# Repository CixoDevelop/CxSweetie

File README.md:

# CxSweetie
This is so sweet tamagotchi based on 7-segment screen!

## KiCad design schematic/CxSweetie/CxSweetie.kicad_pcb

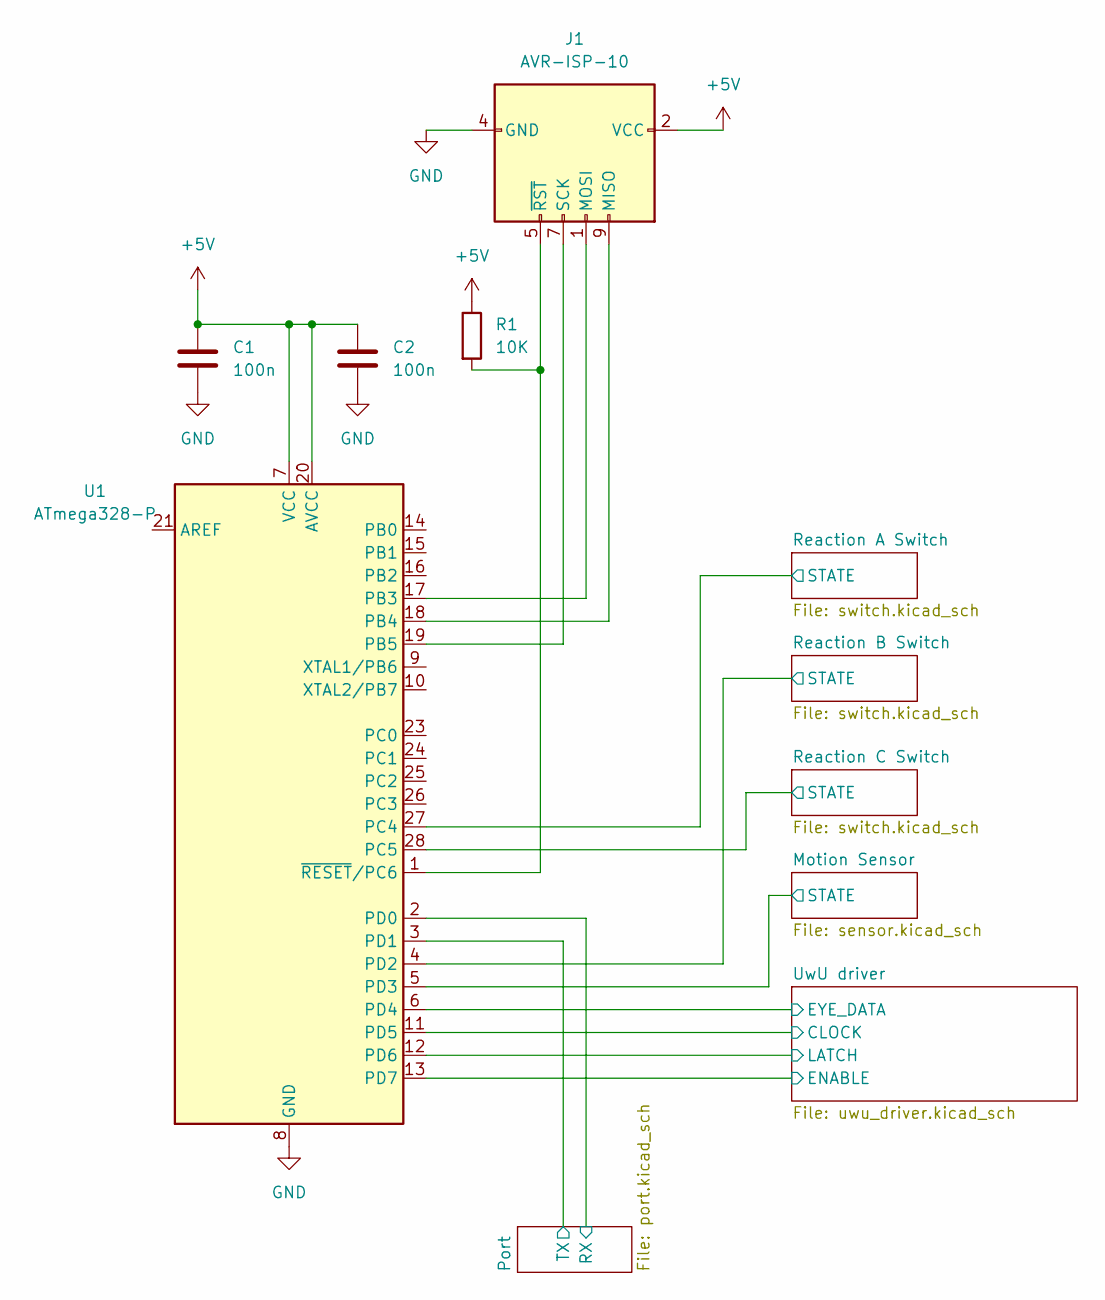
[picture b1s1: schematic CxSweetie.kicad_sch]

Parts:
C1, C2: 100n; CP_Radial_D6.3mm_P2.50mm
J1: AVR-ISP-10; PinHeader_2x05_P2.54mm_Vertical
R1: 10K; R_Axial_DIN0207_L6.3mm_D2.5mm_P7.62mm_Horizontal
U1: ATmega328-P; DIP-28_W7.62mm

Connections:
+5V: C1.1, C2.1, J1.2 (VCC), R1.1, U1.7 (VCC), U1.20 (AVCC); also elsewhere on the board
/Motion Sensor/STATE: U1.5 (PD3); also elsewhere on the board
/Port/RX: U1.2 (PD0); also elsewhere on the board
/Port/TX: U1.3 (PD1); also elsewhere on the board
/Reaction A Switch/STATE: U1.27 (PC4); also elsewhere on the board
/Reaction B Switch/STATE: U1.4 (PD2); also elsewhere on the board
/Reaction C Switch/STATE: U1.28 (PC5); also elsewhere on the board
/UwU driver/CLOCK: U1.11 (PD5); also elsewhere on the board
/UwU driver/ENABLE: U1.13 (PD7); also elsewhere on the board
/UwU driver/EYE_DATA: U1.6 (PD4); also elsewhere on the board
/UwU driver/LATCH: U1.12 (PD6); also elsewhere on the board
GND: C1.2, C2.2, J1.4 (GND), J1.6 (GND), J1.8 (GND), J1.10 (GND), U1.8 (GND), U1.22 (GND); also elsewhere on the board
unnamed: J1.1 (MOSI), U1.17 (PB3)
unnamed: J1.5 (~RST), R1.2, U1.1 (~RESET/PC6)
unnamed: J1.7 (SCK), U1.19 (PB5)
unnamed: J1.9 (MISO), U1.18 (PB4)

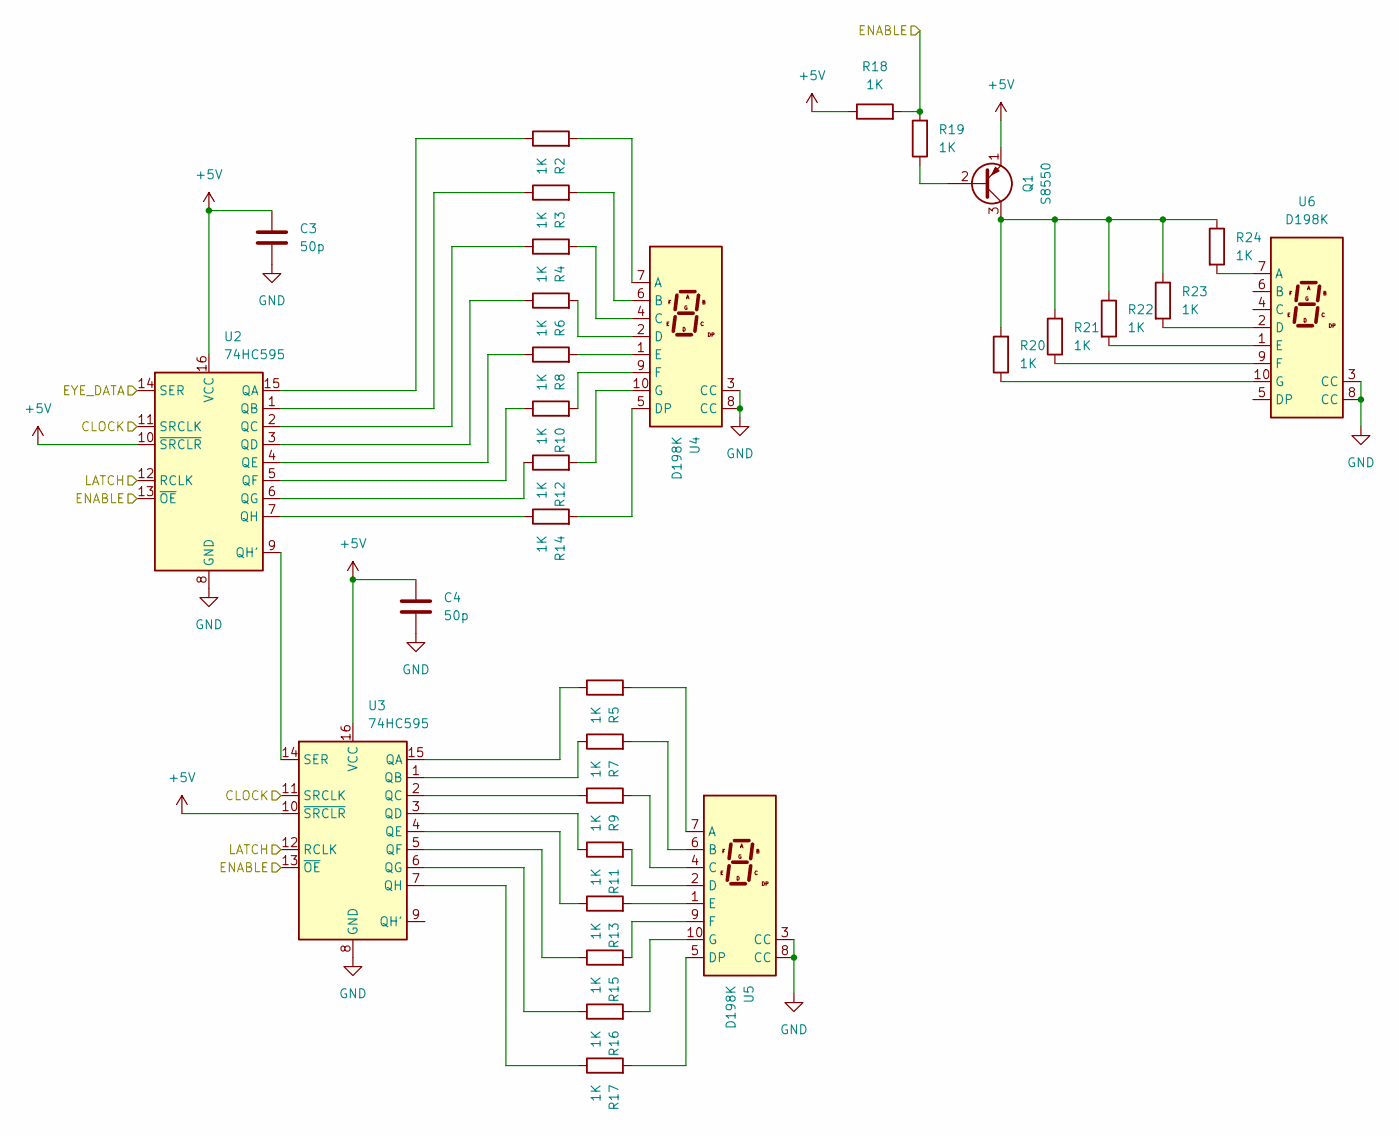
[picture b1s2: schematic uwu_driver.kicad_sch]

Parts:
C3, C4: 50p; CP_Radial_D6.3mm_P2.50mm
Q1: S8550; TO-92_Inline
R2, R3, R4, R5, R6, R7, R8, R9, R10, R11, R12, R13, R14, R15, R16, R17, R18, R19, R20, R21, R22, R23, R24: 1K; R_Axial_DIN0207_L6.3mm_D2.5mm_P7.62mm_Horizontal
U2, U3: 74HC595; DIP-16_W7.62mm
U4, U5, U6: D198K; 7SegmentLED_LTS6760_LTS6780

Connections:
+5V: C3.1, C4.1, Q1.1 (E), R18.1, U2.10 (~SRCLR), U2.16 (VCC), U3.10 (~SRCLR), U3.16 (VCC); also elsewhere on the board
/UwU driver/CLOCK: U2.11 (SRCLK), U3.11 (SRCLK); also elsewhere on the board
/UwU driver/ENABLE: R18.2, R19.2, U2.13 (~OE), U3.13 (~OE); also elsewhere on the board
/UwU driver/EYE_DATA: U2.14 (SER); also elsewhere on the board
/UwU driver/LATCH: U2.12 (RCLK), U3.12 (RCLK); also elsewhere on the board
GND: C3.2, C4.2, U2.8 (GND), U3.8 (GND), U4.3 (CC), U4.8 (CC), U5.3 (CC), U5.8 (CC), U6.3 (CC), U6.8 (CC); also elsewhere on the board
unnamed: Q1.2 (B), R19.1
unnamed: Q1.3 (C), R20.2, R21.2, R22.1, R23.1, R24.1
unnamed: R2.1, U2.15 (QA)
unnamed: R2.2, U4.7 (A)
unnamed: R3.1, U2.1 (QB)
unnamed: R3.2, U4.6 (B)
unnamed: R4.1, U2.2 (QC)
unnamed: R4.2, U4.4 (C)
unnamed: R5.2, U5.7 (A)
unnamed: R6.1, U2.3 (QD)
unnamed: R6.2, U4.2 (D)
unnamed: R7.1, U3.1 (QB)
unnamed: R7.2, U5.6 (B)
unnamed: R8.1, U2.4 (QE)
unnamed: R8.2, U4.1 (E)
unnamed: R9.1, U3.2 (QC)
unnamed: R9.2, U5.4 (C)
unnamed: R10.1, U2.5 (QF)
unnamed: R10.2, U4.9 (F)
unnamed: R11.1, U3.3 (QD)
unnamed: R11.2, U5.2 (D)
unnamed: R12.1, U2.6 (QG)
unnamed: R12.2, U4.10 (G)
unnamed: R13.1, U3.4 (QE)
unnamed: R13.2, U5.1 (E)
unnamed: R14.1, U2.7 (QH)
unnamed: R14.2, U4.5 (DP)
unnamed: R15.1, U3.5 (QF)
unnamed: R15.2, U5.9 (F)
unnamed: R16.1, U3.6 (QG)
unnamed: R16.2, U5.10 (G)
unnamed: R17.1, U3.7 (QH)
unnamed: R17.2, U5.5 (DP)
unnamed: R20.1, U6.10 (G)
unnamed: R21.1, U6.9 (F)
unnamed: R22.2, U6.1 (E)
unnamed: R23.2, U6.2 (D)
unnamed: R24.2, U6.7 (A)
unnamed: U2.9 (QH'), U3.14 (SER)
unnamed: R5.1, U3.15 (QA)

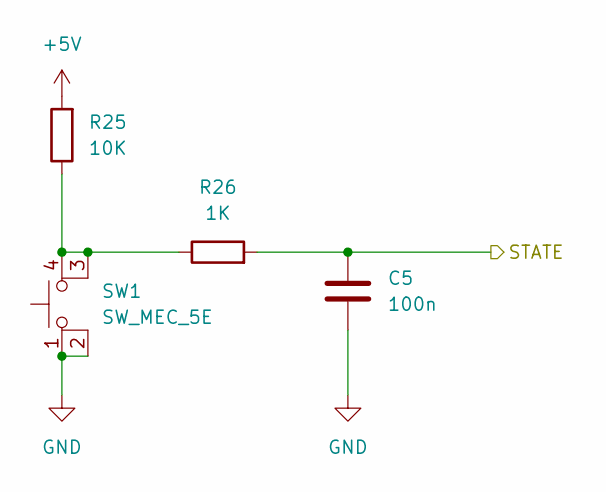
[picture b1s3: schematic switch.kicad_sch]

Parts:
C5: 100n; CP_Radial_D6.3mm_P2.50mm
R25: 10K; R_Axial_DIN0207_L6.3mm_D2.5mm_P7.62mm_Horizontal
R26: 1K; R_Axial_DIN0207_L6.3mm_D2.5mm_P7.62mm_Horizontal
SW1: SW_MEC_5E; SW_Push_2P1T_Toggle_CK_PVA1xxH1xxxxxxV2

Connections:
+5V: R25.2; also elsewhere on the board
/Reaction A Switch/STATE: C5.1, R26.2; also elsewhere on the board
GND: C5.2, SW1.1, SW1.2; also elsewhere on the board
unnamed: R25.1, R26.1, SW1.3 (K), SW1.4 (A)

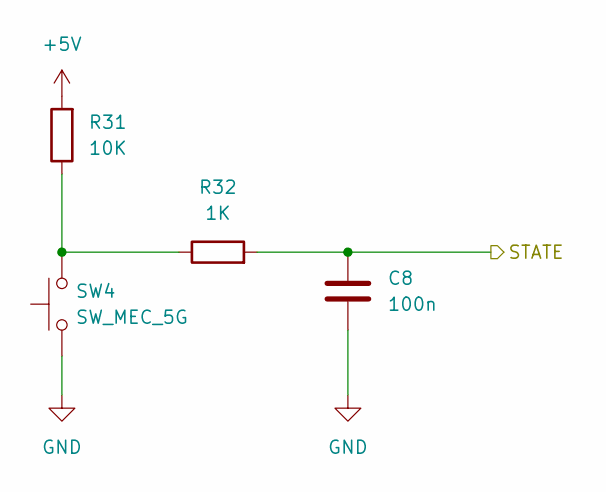
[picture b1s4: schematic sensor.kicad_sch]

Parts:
C8: 100n; CP_Radial_D6.3mm_P2.50mm
R31: 10K; R_Axial_DIN0207_L6.3mm_D2.5mm_P7.62mm_Horizontal
R32: 1K; R_Axial_DIN0207_L6.3mm_D2.5mm_P7.62mm_Horizontal
SW4: SW_MEC_5G; PinHeader_2x02_P2.54mm_Vertical

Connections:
+5V: R31.2; also elsewhere on the board
/Motion Sensor/STATE: C8.1, R32.2; also elsewhere on the board
GND: C8.2, SW4.1 (A), SW4.2 (A); also elsewhere on the board
unnamed: R31.1, R32.1, SW4.3 (B), SW4.4 (B)

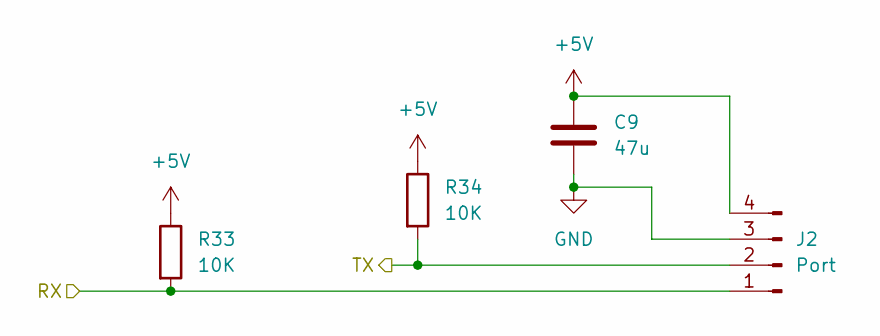
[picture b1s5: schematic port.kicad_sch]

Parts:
C9: 47u; CP_Radial_D6.3mm_P2.50mm
J2: Port; PinHeader_1x04_P2.54mm_Vertical
R33, R34: 10K; R_Axial_DIN0207_L6.3mm_D2.5mm_P7.62mm_Horizontal

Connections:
+5V: C9.1, J2.4, R33.1, R34.1; also elsewhere on the board
/Port/RX: J2.1, R33.2; also elsewhere on the board
/Port/TX: J2.2, R34.2; also elsewhere on the board
GND: C9.2, J2.3; also elsewhere on the board

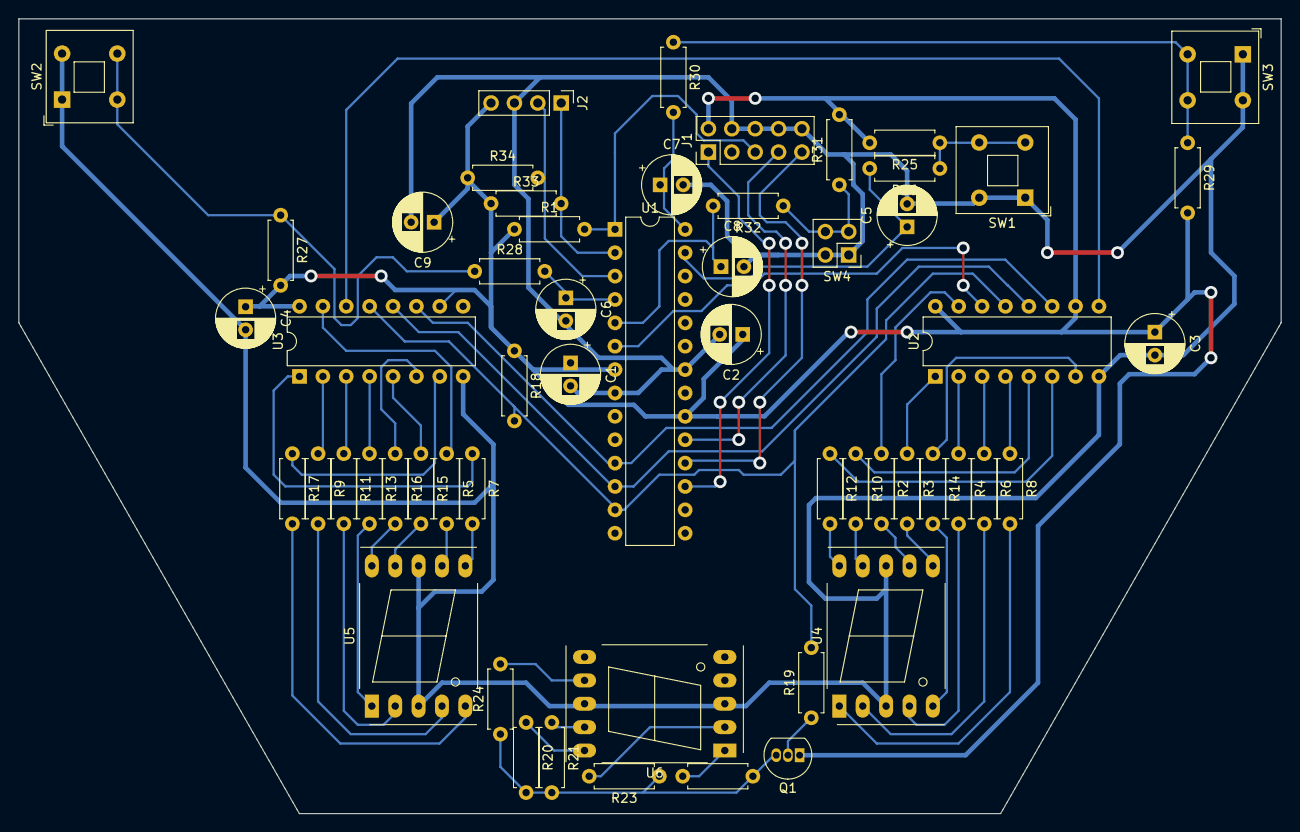
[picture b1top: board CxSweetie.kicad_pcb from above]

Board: 2 copper layers, 137.2 x 86.4 mm, 56 parts (0 on the bottom side), 60 nets.

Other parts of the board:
C6, C7: 100n; CP_Radial_D6.3mm_P2.50mm
R27, R29: 10K; R_Axial_DIN0207_L6.3mm_D2.5mm_P7.62mm_Horizontal
R28, R30: 1K; R_Axial_DIN0207_L6.3mm_D2.5mm_P7.62mm_Horizontal
SW2, SW3: SW_MEC_5E; SW_Push_2P1T_Toggle_CK_PVA1xxH1xxxxxxV2

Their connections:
+5V: R27.2, R29.2; also elsewhere on the board
/Reaction B Switch/STATE: C6.1, R28.2; also elsewhere on the board
/Reaction C Switch/STATE: C7.1, R30.2; also elsewhere on the board
GND: C6.2, C7.2, SW2.1, SW2.2, SW3.1, SW3.2; also elsewhere on the board
unnamed: R27.1, R28.1, SW2.3 (K), SW2.4 (A)
unnamed: R29.1, R30.1, SW3.3 (K), SW3.4 (A)

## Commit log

2022-11-23 First upload to github!
